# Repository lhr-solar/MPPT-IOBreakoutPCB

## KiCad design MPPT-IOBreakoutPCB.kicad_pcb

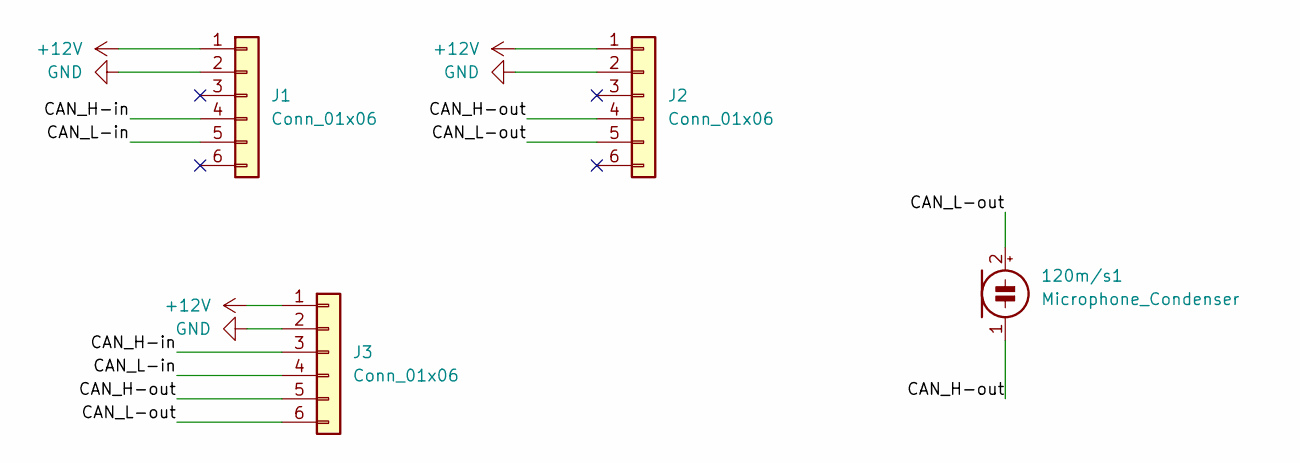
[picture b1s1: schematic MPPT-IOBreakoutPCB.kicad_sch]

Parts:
120m/s1: Microphone_Condenser; R_0603_1608Metric
J1, J2: Conn_01x06; Molex_Microfit3.0_02x03_6-Pin-Vertical-PCB-Receptacle_44769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
J3: Conn_01x06; CONN_SD-44764-001_06_MOL

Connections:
+12V: J1.1, J2.1, J3.1
/CAN_H-in: J1.4, J3.3
/CAN_H-out: 120m/s1.1 (-), J2.4, J3.5
/CAN_L-in: J1.5, J3.4
/CAN_L-out: 120m/s1.2 (+), J2.5, J3.6
GND: J1.2, J2.2, J3.2

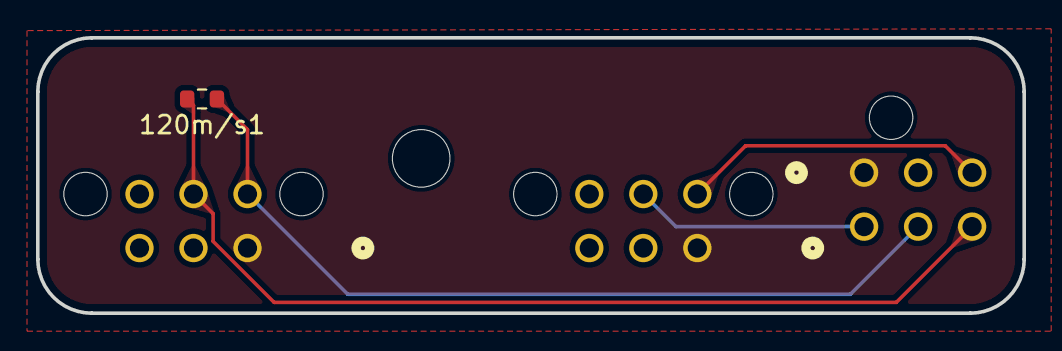
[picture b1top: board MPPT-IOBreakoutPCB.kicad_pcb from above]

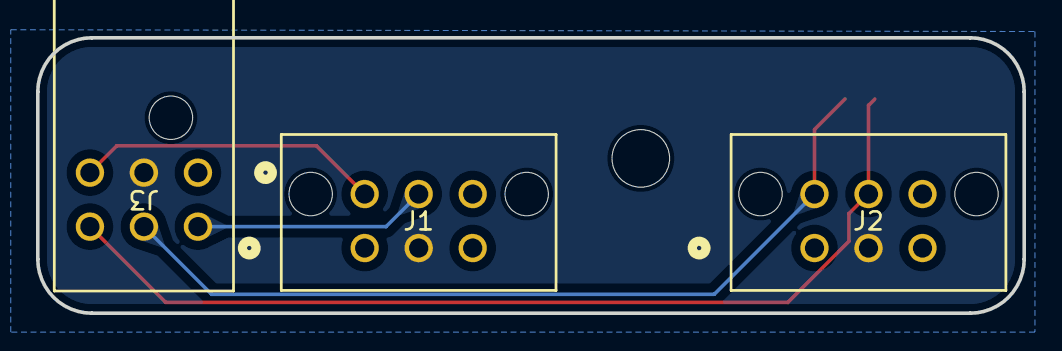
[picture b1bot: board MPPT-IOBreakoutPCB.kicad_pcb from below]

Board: 2 copper layers, 54.8 x 15.3 mm, 4 parts (3 on the bottom side), 6 nets.

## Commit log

2025-10-07 initial
2025-10-07 wrong schem
2025-10-07 right schem
2025-10-07 mppt matched schem
2025-10-07 layout maybe done
2025-10-07 traces
2025-10-07 step
2025-10-12 fixed
